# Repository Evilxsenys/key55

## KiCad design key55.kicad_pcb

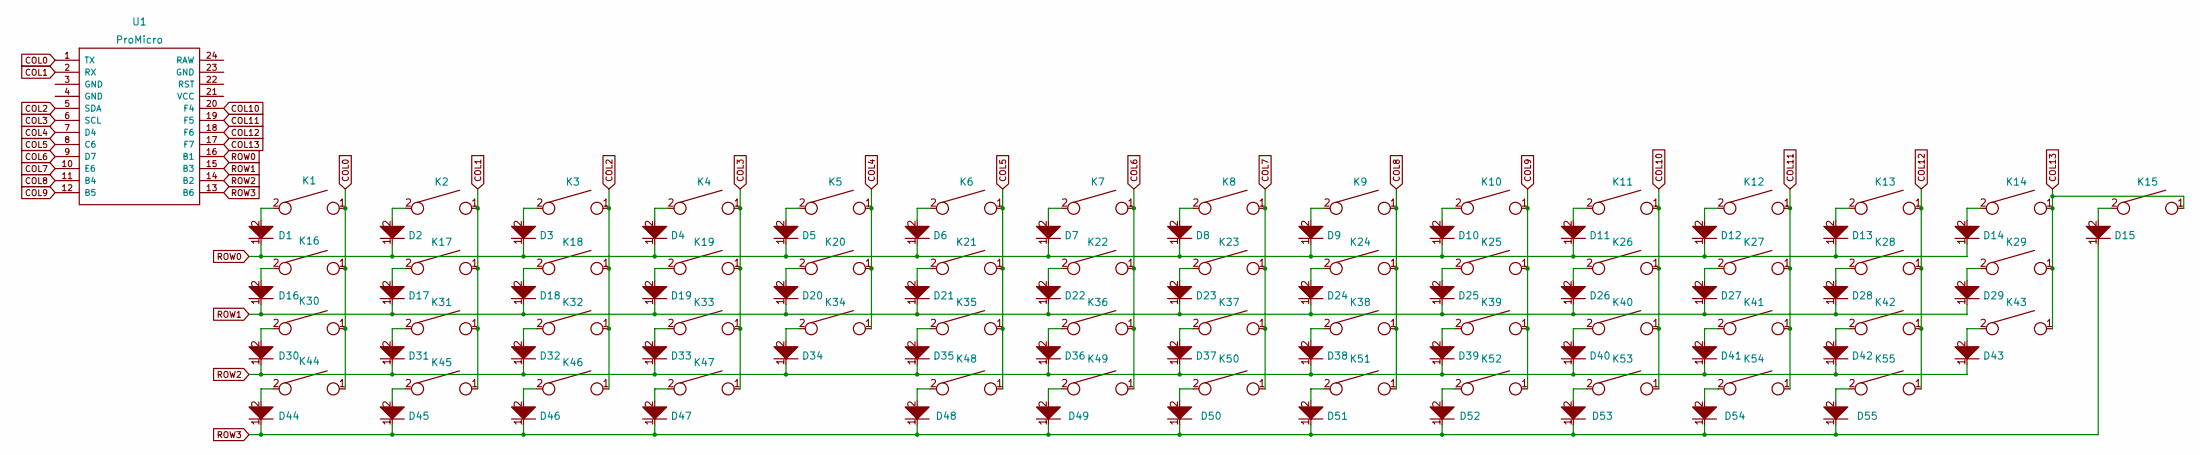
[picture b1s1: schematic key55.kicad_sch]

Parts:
D1, D2, D3, D4, D5, D6, D7, D8, D9, D10, D11, D12, D13, D14, D15, D16, D17, D18, D19, D20, D21, D22, D23, D24, D25, D26, D27, D28, D29, D30, D31, D32, D33, D34, D35, D36, D37, D38, D39, D40, D41, D42, D43, D44, D45, D46, D47, D48, D49, D50, D51, D52, D53, D54, D55: D; MD_Diode
K1, K2, K3, K4, K5, K6, K7, K8, K9, K10, K11, K12, K13, K14, K15, K17, K18, K19, K20, K21, K22, K23, K24, K25, K26, K27, K29, K31, K32, K33, K34, K35, K36, K37, K38, K39, K40, K42, K43, K44, K45, K46, K49, K50, K51, K52, K53, K54, K55: KEYSW; SW_Hotswap_Kailh_MX_1.00u
K16, K41: KEYSW; SW_Hotswap_Kailh_MX_1.25u
K28, K30: KEYSW; SW_Hotswap_Kailh_MX_1.75u
K47: KEYSW; SW_Hotswap_Kailh_MX_2.75u
K48: KEYSW; SW_Hotswap_Kailh_MX_2.25u
U1: ProMicro

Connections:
COL0: K1.1, K16.1, K30.1, K44.1, U1.1 (TX)
COL1: K2.1, K17.1, K31.1, K45.1, U1.2 (RX)
COL2: K3.1, K18.1, K32.1, K46.1, U1.5 (SDA)
COL3: K4.1, K19.1, K33.1, K47.1, U1.6 (SCL)
COL4: K5.1, K20.1, K34.1, U1.7 (D4)
COL5: K6.1, K21.1, K35.1, K48.1, U1.8 (C6)
COL6: K7.1, K22.1, K36.1, K49.1, U1.9 (D7)
COL7: K8.1, K23.1, K37.1, K50.1, U1.10 (E6)
COL8: K9.1, K24.1, K38.1, K51.1, U1.11 (B4)
COL9: K10.1, K25.1, K39.1, K52.1, U1.12 (B5)
COL10: K11.1, K26.1, K40.1, K53.1, U1.20 (F4)
COL11: K12.1, K27.1, K41.1, K54.1, U1.19 (F5)
COL12: K13.1, K28.1, K42.1, K55.1, U1.18 (F6)
COL13: K14.1, K15.1, K29.1, K43.1, U1.17 (F7)
unnamed: D1.2, K1.2
unnamed: D2.2, K2.2
unnamed: D3.2, K3.2
unnamed: D4.2, K4.2
unnamed: D5.2, K5.2
unnamed: D6.2, K6.2
unnamed: D7.2, K7.2
unnamed: D8.2, K8.2
unnamed: D9.2, K9.2
unnamed: D10.2, K10.2
unnamed: D11.2, K11.2
unnamed: D12.2, K12.2
unnamed: D13.2, K13.2
unnamed: D14.2, K14.2
unnamed: D15.2, K15.2
unnamed: D16.2, K16.2
unnamed: D17.2, K17.2
unnamed: D18.2, K18.2
unnamed: D19.2, K19.2
unnamed: D20.2, K20.2
unnamed: D21.2, K21.2
unnamed: D22.2, K22.2
unnamed: D23.2, K23.2
unnamed: D24.2, K24.2
unnamed: D25.2, K25.2
unnamed: D26.2, K26.2
unnamed: D27.2, K27.2
unnamed: D28.2, K28.2
unnamed: D29.2, K29.2
unnamed: D30.2, K30.2
unnamed: D31.2, K31.2
unnamed: D32.2, K32.2
unnamed: D33.2, K33.2
unnamed: D34.2, K34.2
unnamed: D35.2, K35.2
unnamed: D36.2, K36.2
unnamed: D37.2, K37.2
unnamed: D38.2, K38.2
unnamed: D39.2, K39.2
unnamed: D40.2, K40.2
unnamed: D41.2, K41.2
unnamed: D42.2, K42.2
unnamed: D43.2, K43.2
unnamed: D44.2, K44.2
unnamed: D45.2, K45.2
unnamed: D46.2, K46.2
unnamed: D47.2, K47.2
unnamed: D48.2, K48.2
unnamed: D49.2, K49.2
unnamed: D50.2, K50.2
unnamed: D51.2, K51.2
unnamed: D52.2, K52.2
unnamed: D53.2, K53.2
unnamed: D54.2, K54.2
unnamed: D55.2, K55.2
ROW0: D1.1, D2.1, D3.1, D4.1, D5.1, D6.1, D7.1, D8.1, D9.1, D10.1, D11.1, D12.1, D13.1, D14.1, U1.16 (B1)
ROW1: D16.1, D17.1, D18.1, D19.1, D20.1, D21.1, D22.1, D23.1, D24.1, D25.1, D26.1, D27.1, D28.1, D29.1, U1.15 (B3)
ROW2: D30.1, D31.1, D32.1, D33.1, D34.1, D35.1, D36.1, D37.1, D38.1, D39.1, D40.1, D41.1, D42.1, D43.1, U1.14 (B2)
ROW3: D15.1, D44.1, D45.1, D46.1, D47.1, D48.1, D49.1, D50.1, D51.1, D52.1, D53.1, D54.1, D55.1, U1.13 (B6)

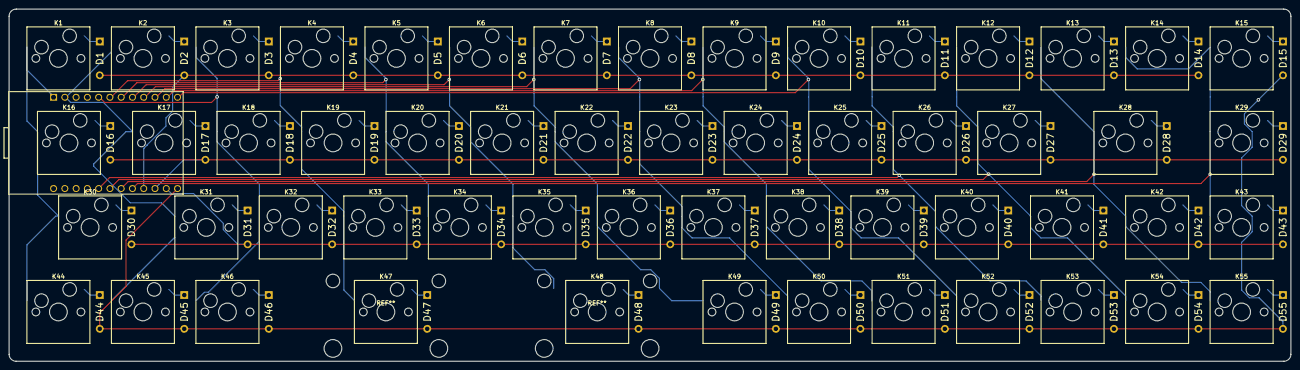
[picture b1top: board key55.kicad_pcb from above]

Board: 2 copper layers, 288.9 x 79.4 mm, 111 parts (1 on the bottom side), 73 nets.

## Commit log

2023-01-14 Start
2023-01-14 Add submodules
2023-01-14 Process nahuy of working
2023-01-15 Key55 V0.1
    pcb done
2023-01-15 Added footprint of my arduino
